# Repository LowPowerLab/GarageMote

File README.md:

GarageMote
==========

Moteino garage controller shield

###License
[CC-BY-SA 3.0](http://creativecommons.org/licenses/by-sa/3.0/us/)

###Writeup
http://lowpowerlab.com/blog/2013/10/11/raspberrypi-home-automation-gateway-hardware-and-demo/

###Video demonstration
http://www.youtube.com/watch?v=ucMsGSdcs2U

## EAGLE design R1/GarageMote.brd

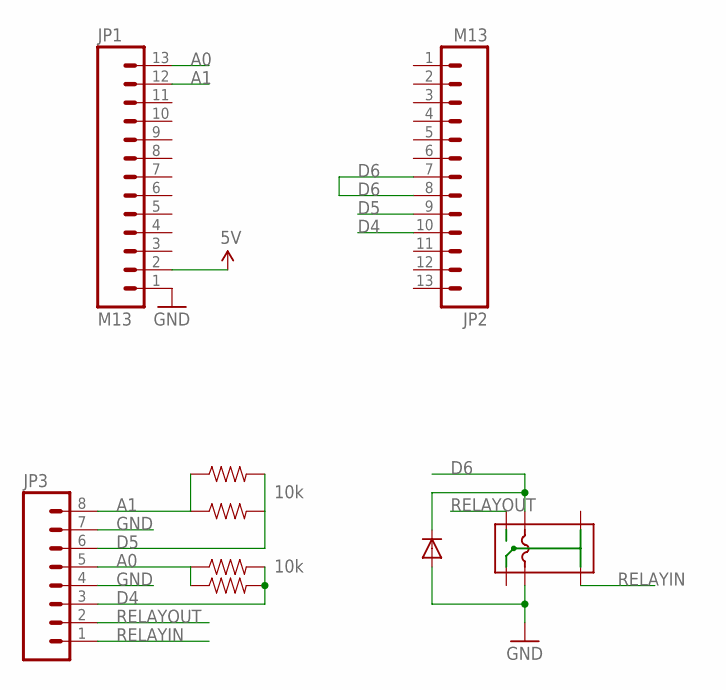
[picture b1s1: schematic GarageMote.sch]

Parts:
1N4001: DIODEUPRIGHT; DIODE_UPRIGHT
JP1, JP2: M13; 1X13
JP3: M081X08; 1X08
JRC-2F: JRC-23F
R1, R2: 10k; 0603-RES
R3, R4: RESISTOR1/4W; AXIAL-1/4W

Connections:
5V: JP1.2
A0: JP1.13, JP3.5, R1.1, R3.P$1 (1)
A1: JP1.12, JP3.8, R2.1, R4.P$1 (1)
D4: JP2.10, JP3.3, R1.2, R3.P$2 (2)
D5: JP2.9, JP3.6, R2.2, R4.P$2 (2)
D6: 1N4001.CATHODE_MINUS, JP2.7, JP2.8, JRC-2F.COIL1
GND: 1N4001.ANODE_PLUS, JP1.1, JP3.4, JP3.7, JRC-2F.COIL2
RELAYIN: JP3.1, JRC-2F.COM2
RELAYOUT: JP3.2, JRC-2F.SW1

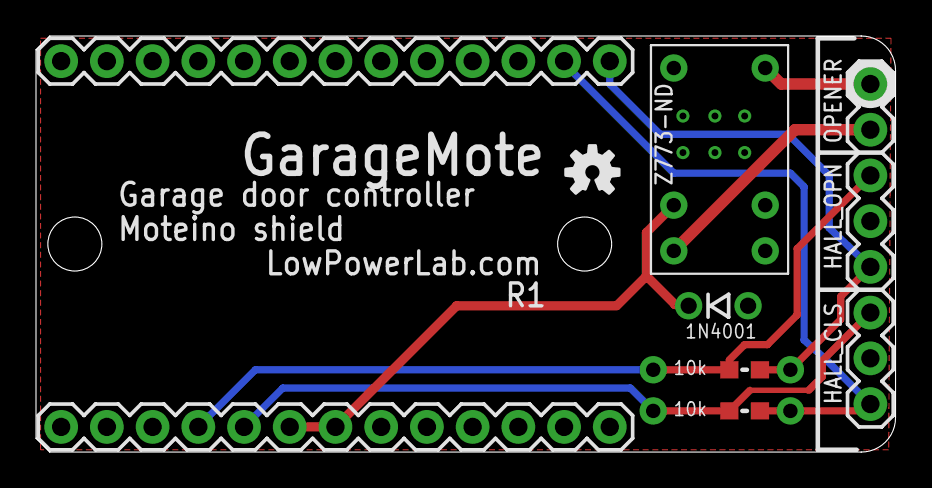
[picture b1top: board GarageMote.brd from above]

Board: 2 copper layers, 47.8 x 23.1 mm, 11 parts (1 on the bottom side), 8 nets.

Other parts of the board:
U$1, U$2: OSHW-LOGO-S

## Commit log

2013-10-11 Add Eagle schematic and board layout
2021-01-08 Add R2

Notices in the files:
parts and their libraries:
SparkFun-Connectors: Licensing: CC v3.0 Share-Alike You are welcome to use this library for commercial purposes.
